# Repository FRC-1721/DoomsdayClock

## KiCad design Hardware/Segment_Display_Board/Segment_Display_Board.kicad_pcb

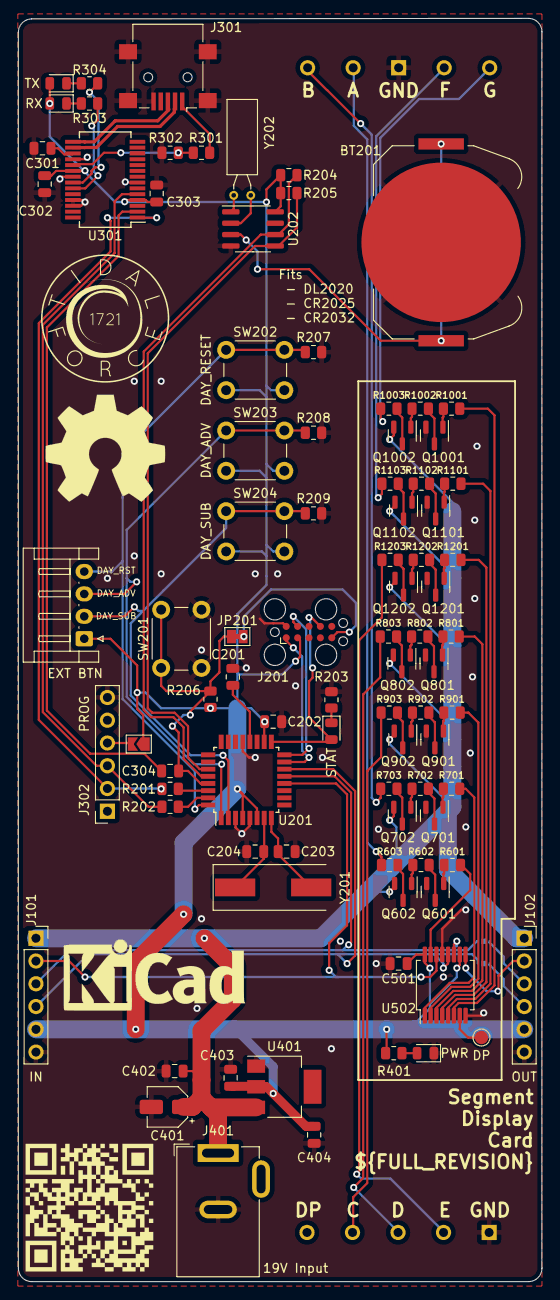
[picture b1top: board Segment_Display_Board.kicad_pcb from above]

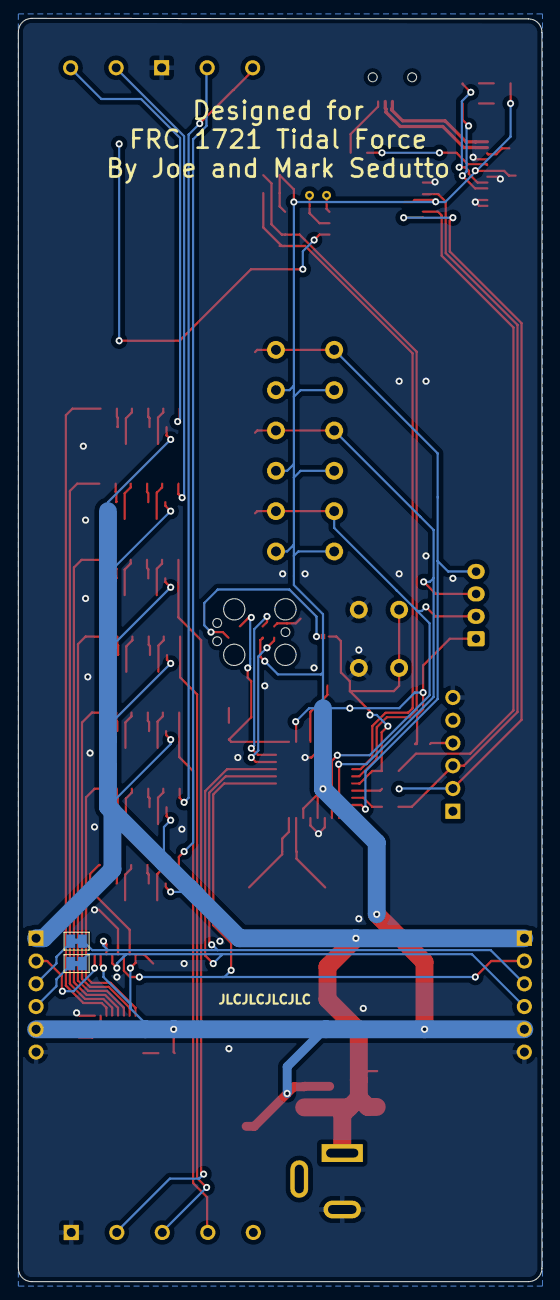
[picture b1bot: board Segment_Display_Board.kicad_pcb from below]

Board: 2 copper layers, 58.4 x 141.0 mm, 91 parts (2 on the bottom side), 85 nets.

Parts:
BT201: 3v; BatteryHolder_Keystone_3034_1x20mm
C201, C202: 100nf; C_0805_2012Metric
C203, C204: 22pf; C_0805_2012Metric
C301, C302, C303, C304, C402, C403, C501: 100nF; C_0805_2012Metric
C401: 10uf; CP_Elec_4x3
C404: 1uF; C_0805_2012Metric
D201: STAT; LED_0805_2012Metric
D301: RX; LED_0805_2012Metric
D302: TX; LED_0805_2012Metric
D401: PWR; LED_0805_2012Metric
J101: IN; PinSocket_1x06_P2.54mm_Vertical
J102: OUT; PinSocket_1x06_P2.54mm_Vertical
J201: Tag Connect; Tag-Connect_TC2050-IDC-FP_2x05_P1.27mm_Vertical
J202: EXT BTN; JST_EH_S4B-EH_1x04_P2.50mm_Horizontal
J301: USB_B_Micro; USB_Mini-B_Lumberg_2486_01_Horizontal
J302: PROG; PinSocket_1x06_P2.54mm_Vertical
J401: 19V Input; BarrelJack_GCT_DCJ200-10-A_Horizontal
JP201: RSTBridge; SolderJumper-2_P1.3mm_Bridged_Pad1.0x1.5mm
JP301: SolderJumper_2_Open; SolderJumper-2_P1.3mm_Open_TrianglePad1.0x1.5mm
JP501, JP502: SolderJumper_2_Bridged; SolderJumper-2_P1.3mm_Bridged_Pad1.0x1.5mm
Q601, Q701, Q801, Q901, Q1001, Q1101, Q1201: MMBT3904; SOT-23
Q602, Q702, Q802, Q902, Q1002, Q1102, Q1202: MMBT3906; SOT-23
R201, R202, R203, R206, R303, R304, R401: 1K; R_0805_2012Metric
R204, R205, R207, R208, R209, R302, R601, R701, R801, R901, R1001, R1101, R1201: 10K; R_0805_2012Metric
R301: 4K7; R_0805_2012Metric
R602, R702, R802, R902, R1002, R1102, R1202: 2K2; R_0805_2012Metric
R603, R703, R803, R903, R1003, R1103, R1203: TBD; R_0805_2012Metric
SW201: RESET; SW_PUSH_6mm_H5mm
SW202: DAY_RESET; SW_PUSH_6mm_H5mm
SW203: DAY_ADV; SW_PUSH_6mm_H5mm
SW204: DAY_SUB; SW_PUSH_6mm_H5mm
TP501: DP; TestPoint_Pad_D1.5mm
U201: ATmega328P-A; TQFP-32_7x7mm_P0.8mm
U202: DS1307Z+; SOIC-8_3.9x4.9mm_P1.27mm
U301: FT232RL; SSOP-28_5.3x10.2mm_P0.65mm
U401: NCV1117ST50T3G; SOT-223
U501: 5inSegment
U502: SN74HC595
Y201: 16mHz; Crystal_SMD_HC49-SD
Y202: 32.768kHz; Crystal_C38-LF_D3.0mm_L8.0mm_Horizontal

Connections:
+3.3V: C301.1, U301.17 (3V3OUT)
+5V: C202.1, C302.1, C303.1, C403.1, C404.1, C501.1, D301.2 (A), D302.2 (A), J101.5, J102.5, J201.2, J202.1, JP301.1 (A), R204.1, R205.1, R206.1, R401.1, SW202.2, SW203.2, SW204.2, U201.4 (VCC), U201.6 (VCC), U201.18 (AVCC), U202.8 (VCC), U301.4 (VCCIO), U301.20 (VCC), U401.2 (VO), U502.10 (SRCLR), U502.16 (VCC)
+19V: C401.1, C402.1, J101.1, J102.1, J401.1, Q602.2 (E), Q702.2 (E), Q802.2 (E), Q902.2 (E), Q1002.2 (E), Q1102.2 (E), Q1202.2 (E), U401.3 (VI)
/C_OUT: J101.3, JP502.1 (A), U201.13 (PB1), U502.11 (SRCLK)
/D_OUT: J101.2, U201.12 (PB0), U502.14 (SER)
/Display Card/CLOCK_OUT: J102.3, JP502.2 (B)
/Display Card/DATA_OUT: J102.2, U502.9 (QH')
/Display Card/LATCH_OUT: J102.4, JP501.2 (B)
/Display Card/SEG_A: R601.1, U502.15 (QA)
/Display Card/SEG_A_LAMP: R603.2, U501.2 (A)
/Display Card/SEG_B: R701.1, U502.1 (QB)
/Display Card/SEG_B_LAMP: R703.2, U501.1 (B)
/Display Card/SEG_C: R901.1, U502.2 (QC)
/Display Card/SEG_C_LAMP: R903.2, U501.7 (C)
/Display Card/SEG_D: R801.1, U502.3 (QD)
/Display Card/SEG_D_LAMP: R803.2, U501.8 (D)
/Display Card/SEG_E: R1201.1, U502.4 (QE)
/Display Card/SEG_E_LAMP: R1203.2, U501.9 (E)
/Display Card/SEG_F: R1101.1, U502.5 (QF)
/Display Card/SEG_F_LAMP: R1103.2, U501.4 (F)
/Display Card/SEG_G: R1001.1, U502.6 (QG)
/Display Card/SEG_G_LAMP: R1003.2, U501.5 (G)
/L_OUT: J101.4, JP501.1 (A), U201.14 (PB2), U502.12 (RCLK)
/MCU/DAY_ADVANCE: J202.3, R208.1, SW203.1, U201.1 (PD3)
/MCU/DAY_RESET: J202.4, R207.1, SW202.1, U201.32 (PD2)
/MCU/DAY_SUBTRACT: J202.2, R209.1, SW204.1, U201.2 (PD4)
/MCU/ICSP_MISO: J201.9, U201.16 (PB4)
/MCU/ICSP_MOSI: J201.1, U201.15 (PB3)
/MCU/ICSP_RST: J201.5, JP201.2 (B)
/MCU/ICSP_SCK: D201.2 (A), J201.7, U201.17 (PB5)
/MCU/RST: C304.1, JP201.1 (A), R206.2, SW201.1, U201.29 (~RESET/PC6)
/MCU/RXD: J302.2, R201.2, U301.1 (TXD)
/MCU/SCL: R204.2, U201.28 (PC5), U202.6 (SCL)
/MCU/SDA: R205.2, U201.27 (PC4), U202.5 (SDA)
/MCU/TXD: J302.3, R202.2, U301.5 (RXD)
/USB/USB+: J301.3 (D+), U301.15 (USBD+)
/USB/USB-: J301.2 (D-), U301.16 (USBD-)
GND: BT201.2 (-), C201.2, C202.2, C203.2, C204.2, C301.2, C302.2, C303.2, C401.2, C402.2, C403.2, C404.2, C501.2, D401.1 (K), J101.6, J102.6, J201.10, J301.5 (GND), J301.6 (Shield), J302.6, J401.2, Q601.2 (E), Q701.2 (E), Q801.2 (E), Q901.2 (E), Q1001.2 (E), Q1101.2 (E), Q1201.2 (E), R203.1, R207.2, R208.2, R209.2, R302.1, SW201.2, U201.3 (GND), U201.5 (GND), U201.21 (GND), U202.4 (GND), U301.7 (GND), U301.18 (GND), U301.21 (GND), U301.25 (AGND), U301.26 (TEST), U401.1 (GND), U501.3 (GND), U501.10 (GND), U502.8 (GND), U502.13 (OE)
unnamed: BT201.1 (+), U202.3 (VBAT)
unnamed: C201.1, U201.20 (AREF)
unnamed: C203.1, U201.8 (XTAL2/PB7), Y201.2
unnamed: C204.1, U201.7 (XTAL1/PB6), Y201.1
unnamed: C304.2, U301.2 (DTR)
unnamed: D201.1 (K), R203.2
unnamed: D301.1 (K), R303.2
unnamed: D302.1 (K), R304.1
unnamed: D401.2 (A), R401.2
unnamed: J302.4, JP301.2 (B)
unnamed: Q601.1 (B), R601.2
unnamed: Q601.3 (C), R602.1
unnamed: Q602.1 (B), R602.2
unnamed: Q602.3 (C), R603.1
unnamed: Q701.1 (B), R701.2
unnamed: Q701.3 (C), R702.1
unnamed: Q702.1 (B), R702.2
unnamed: Q702.3 (C), R703.1
unnamed: Q801.1 (B), R801.2
unnamed: Q801.3 (C), R802.1
unnamed: Q802.1 (B), R802.2
unnamed: Q802.3 (C), R803.1
unnamed: Q901.1 (B), R901.2
unnamed: Q901.3 (C), R902.1
unnamed: Q902.1 (B), R902.2
unnamed: Q902.3 (C), R903.1
unnamed: Q1001.1 (B), R1001.2
unnamed: Q1001.3 (C), R1002.1
unnamed: Q1002.1 (B), R1002.2
unnamed: Q1002.3 (C), R1003.1
unnamed: Q1101.1 (B), R1101.2
unnamed: Q1101.3 (C), R1102.1
unnamed: Q1102.1 (B), R1102.2
unnamed: Q1102.3 (C), R1103.1
unnamed: Q1201.1 (B), R1201.2
unnamed: Q1201.3 (C), R1202.1
unnamed: Q1202.1 (B), R1202.2
unnamed: Q1202.3 (C), R1203.1
unnamed: R201.1, U201.30 (PD0)
unnamed: R202.1, U201.31 (PD1)
unnamed: R301.1, R302.2, U301.19 (~RESET)
unnamed: R303.1, U301.23 (CBUS0)
unnamed: R304.2, U301.22 (CBUS1)
unnamed: U202.1 (X1), Y202.2
unnamed: U202.2 (X2), Y202.1
unnamed: TP501.1, U502.7 (QH)
VBUS: J301.1 (VBUS), R301.2

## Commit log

2022-12-17 Bump kicad libs and add more 3d model
2022-12-17 Bump
2022-12-27 Create empty middle segment
2022-12-27 Create colon segment
2022-12-31 Recess colon
2023-01-01 Cleanout for esp32
2023-01-03 Bump colon
2023-01-10 Make new stencil holder
